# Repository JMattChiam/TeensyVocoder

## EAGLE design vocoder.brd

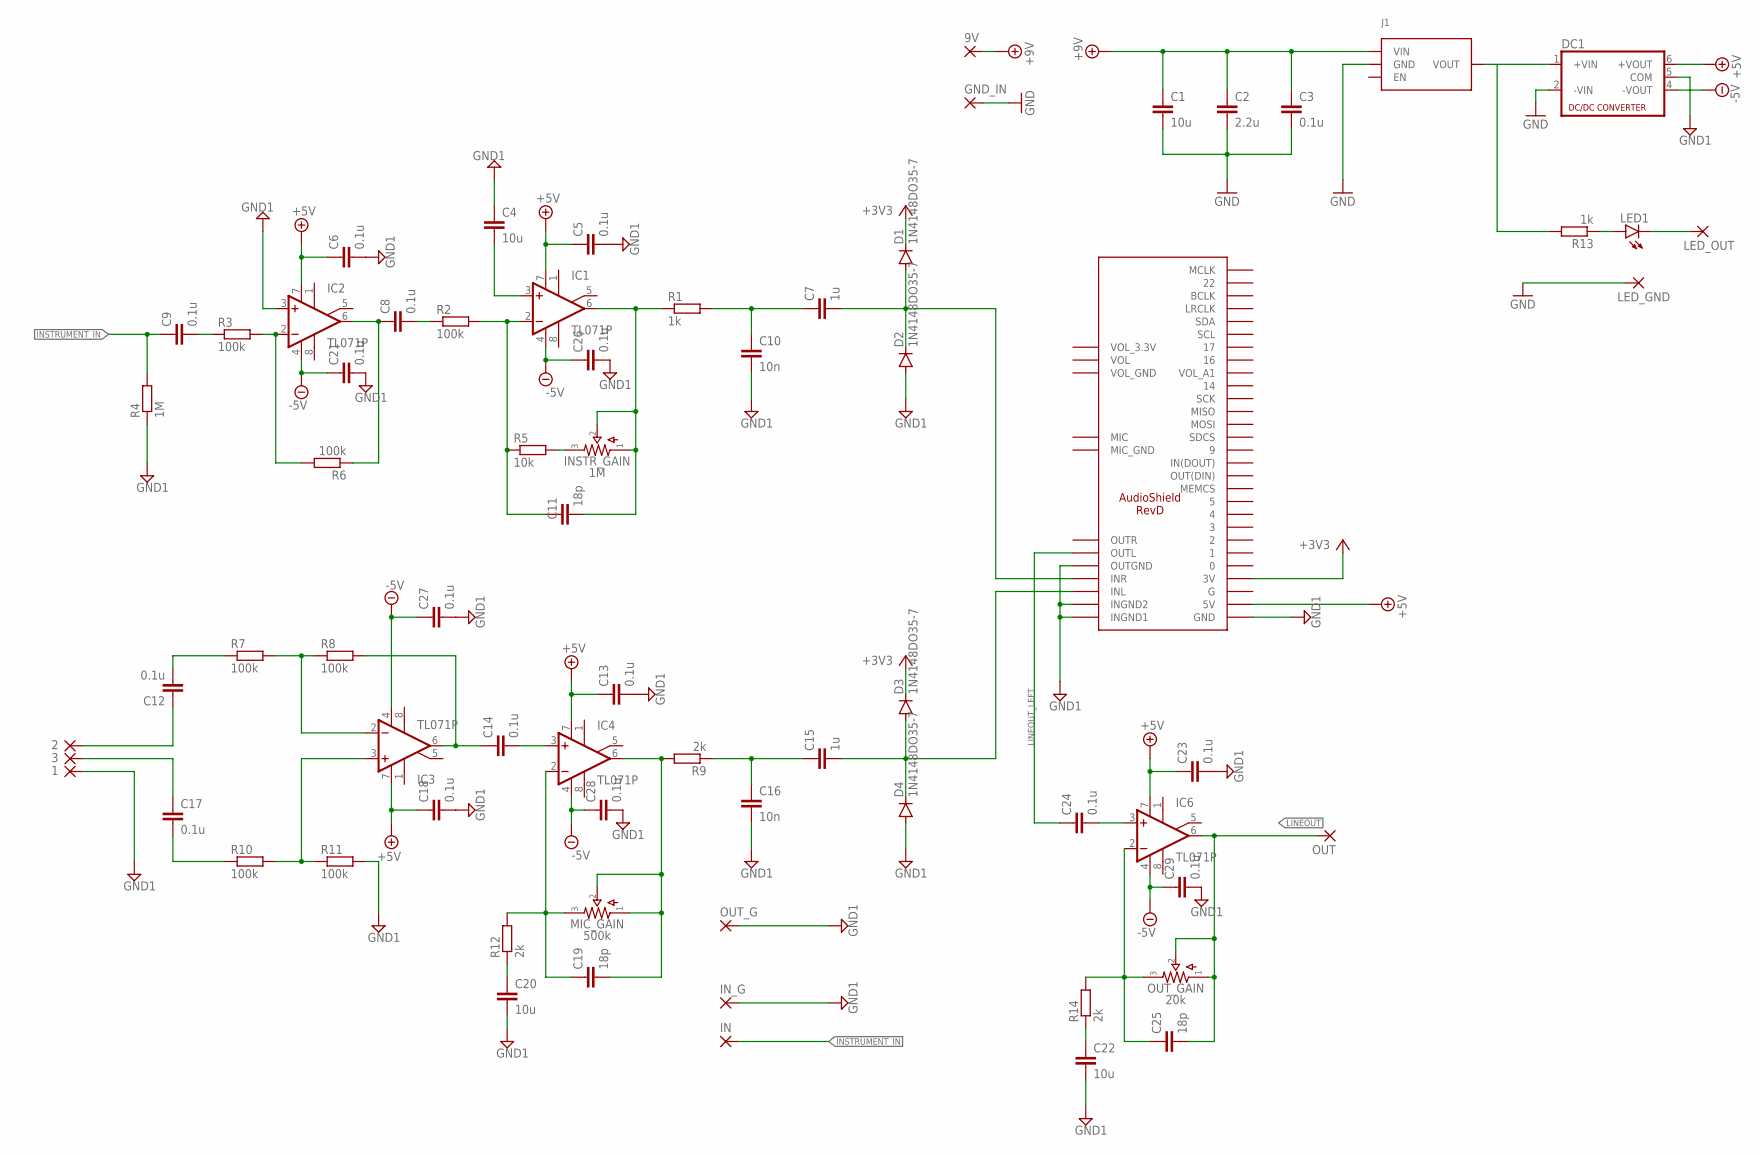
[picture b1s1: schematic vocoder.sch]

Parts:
1, 2, 3, 9V: 1,6/0,8
C1, C4, C20, C22: 10u; C5B2.5
C2: 2.2u; C5B2.5
C3, C5, C6, C8, C9, C12, C13, C14, C17, C18, C21, C23, C24, C26, C27, C28, C29: 0.1u; C0805
C7, C15: 1u; C0805
C10, C16: 10n; C0805
C11, C19, C25: 18p; C0805
D1, D2, D3, D4: 1N4148DO35-7; DO35-7
DC1: NMA
GND_IN: 1,6/0,8
IC1, IC2, IC3, IC4, IC6: TL071P; DIL08
IN: 1,6/0,8
INSTR_GAIN: 1M; 16MM_PADS.1
IN_G: 1,6/0,8
J1: DCDC_MINI_CONVERTER
LED1: LED5MM
LED_GND: 1,6/0,8
LED_OUT: 1,6/0,8
MIC_GAIN: 500k; 16MM_PADS.1
MOD1: AUDIOSHIELD-REVD
OUT: 1,6/0,8
OUT_G: 1,6/0,8
OUT_GAIN: 20k; 16MM_PADS.1
R1, R13: 1k; R0805
R2, R3, R6, R7, R8, R10, R11: 100k; R0805
R4: 1M; R0805
R5: 10k; R0805
R9, R12, R14: 2k; R0805

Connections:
+3V3: D1.C, D3.C, MOD1.3V
+5V: C5.1, C6.1, C13.1, C18.1, C23.1, DC1.6 (+VOUT), IC1.7 (V+), IC2.7 (V+), IC3.7 (V+), IC4.7 (V+), IC6.7 (V+), MOD1.5V
+9V: 9V.1, C1.1, C2.1, C3.1, J1.VIN
-5V: C21.1, C26.1, C27.1, C28.1, C29.1, DC1.4 (-VOUT), IC1.4 (V-), IC2.4 (V-), IC3.4 (V-), IC4.4 (V-), IC6.4 (V-)
GND: C1.2, C2.2, C3.2, DC1.2 (-VIN), GND_IN.1, J1.GND, LED_GND.1
GND1: 1.1, C4.1, C5.2, C6.2, C10.2, C13.2, C16.2, C18.2, C20.2, C21.2, C22.2, C23.2, C26.2, C27.2, C28.2, C29.2, D2.A, D4.A, DC1.5 (COM), IC2.3 (+IN), IN_G.1, MOD1.GND, MOD1.INGND1, MOD1.INGND2, MOD1.OUTGND, OUT_G.1, R4.1, R11.2
INSTRUMENT_IN: C9.1, IN.1, R4.2
LINEOUT: C25.2, IC6.6 (OUT), OUT.1, OUT_GAIN.1, OUT_GAIN.2
LINEOUT_LEFT: C24.1, MOD1.OUTL
unnamed: LED1.A, R13.1
unnamed: C11.1, IC1.2 (-IN), R2.2, R5.1
unnamed: C7.1, C10.1, R1.2
unnamed: C4.2, IC1.3 (+IN)
unnamed: LED1.K (C), LED_OUT.1
unnamed: C11.2, IC1.6 (OUT), INSTR_GAIN.1, INSTR_GAIN.2, R1.1
unnamed: C7.2, D1.A, D2.C, MOD1.INR
unnamed: 2.1, C12.1
unnamed: C12.2, R7.1
unnamed: DC1.1 (+VIN), J1.VOUT, R13.2
unnamed: 3.1, C17.1
unnamed: C17.2, R10.1
unnamed: C14.1, IC3.6 (OUT), R8.2
unnamed: C25.1, IC6.2 (-IN), OUT_GAIN.3, R14.2
unnamed: C22.1, R14.1
unnamed: C24.2, IC6.3 (+IN)
unnamed: C19.1, IC4.2 (-IN), MIC_GAIN.3, R12.2
unnamed: C20.1, R12.1
unnamed: C19.2, IC4.6 (OUT), MIC_GAIN.1, MIC_GAIN.2, R9.2
unnamed: C15.1, C16.1, R9.1
unnamed: C15.2, D3.A, D4.C, MOD1.INL
unnamed: C8.1, IC2.6 (OUT), R6.1
unnamed: C9.2, R3.1
unnamed: C8.2, R2.1
unnamed: INSTR_GAIN.3, R5.2
unnamed: IC2.2 (-IN), R3.2, R6.2
unnamed: IC3.3 (+IN), R10.2, R11.1
unnamed: IC3.2 (-IN), R7.2, R8.1
unnamed: C14.2, IC4.3 (+IN)

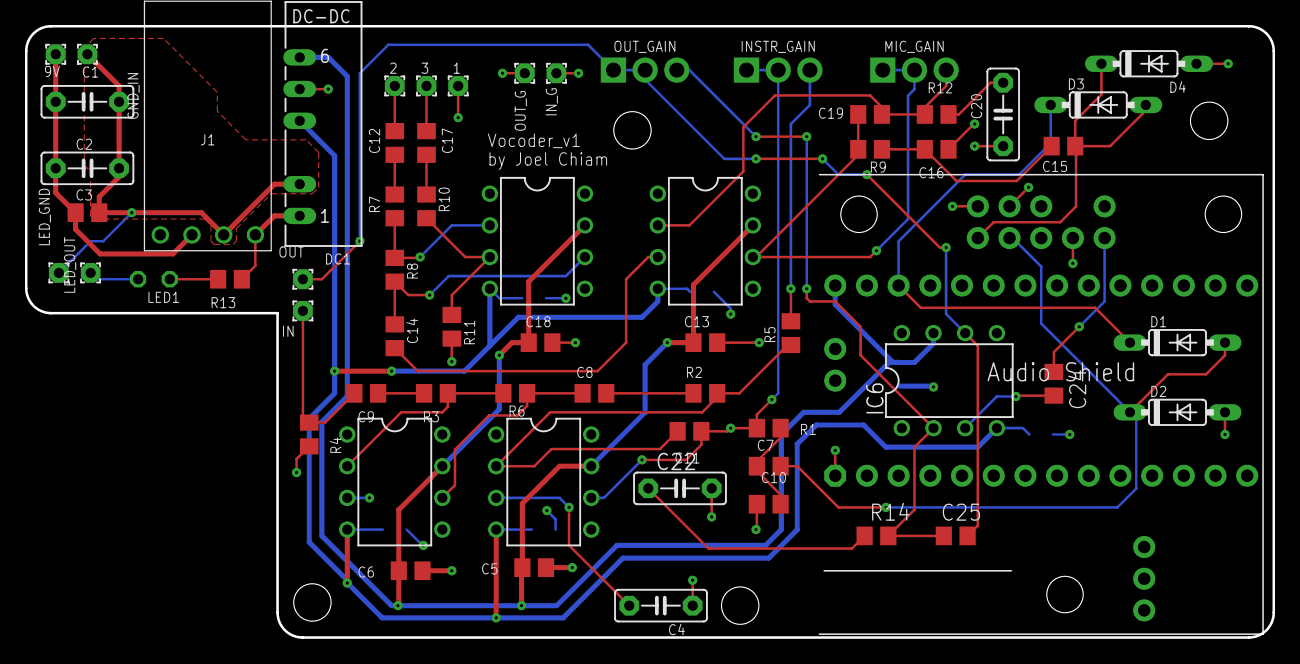
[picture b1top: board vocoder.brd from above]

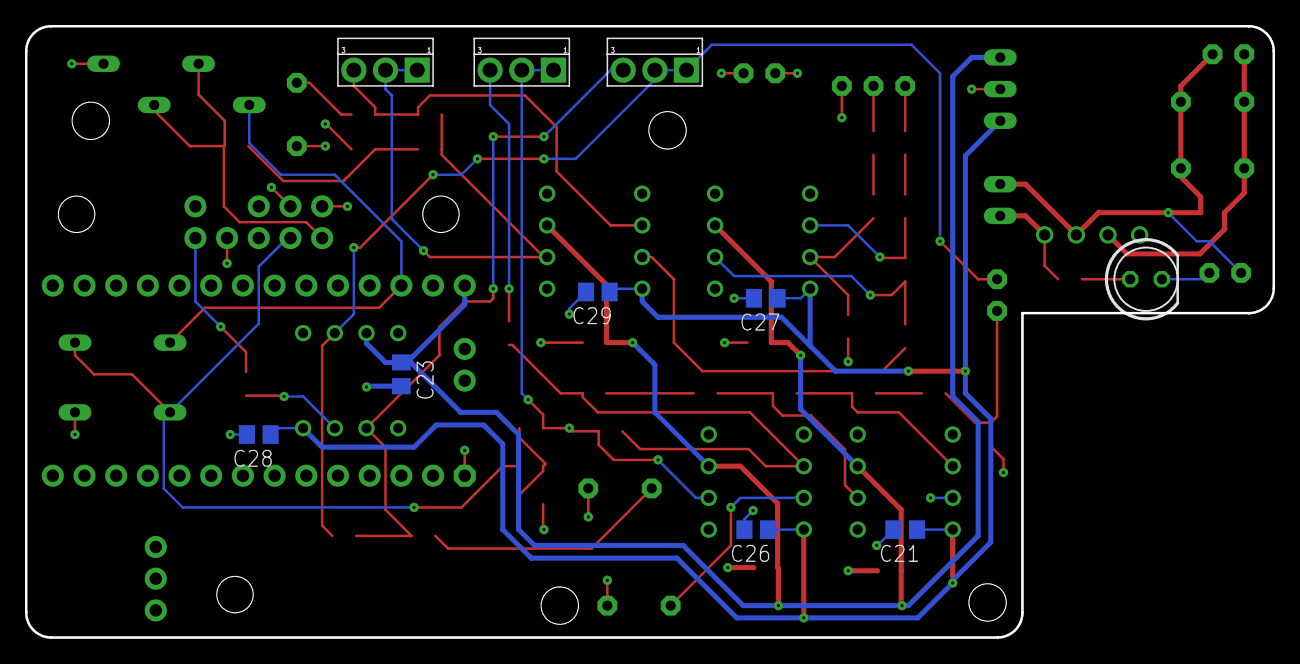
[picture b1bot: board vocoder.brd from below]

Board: 4 copper layers, 100.0 x 49.0 mm, 70 parts (10 on the bottom side), 38 nets.

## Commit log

2023-09-24 Rename Attenuation.brd to vocoder.brd
2023-09-24 Rename Attenuation.sch to vocoder.sch
